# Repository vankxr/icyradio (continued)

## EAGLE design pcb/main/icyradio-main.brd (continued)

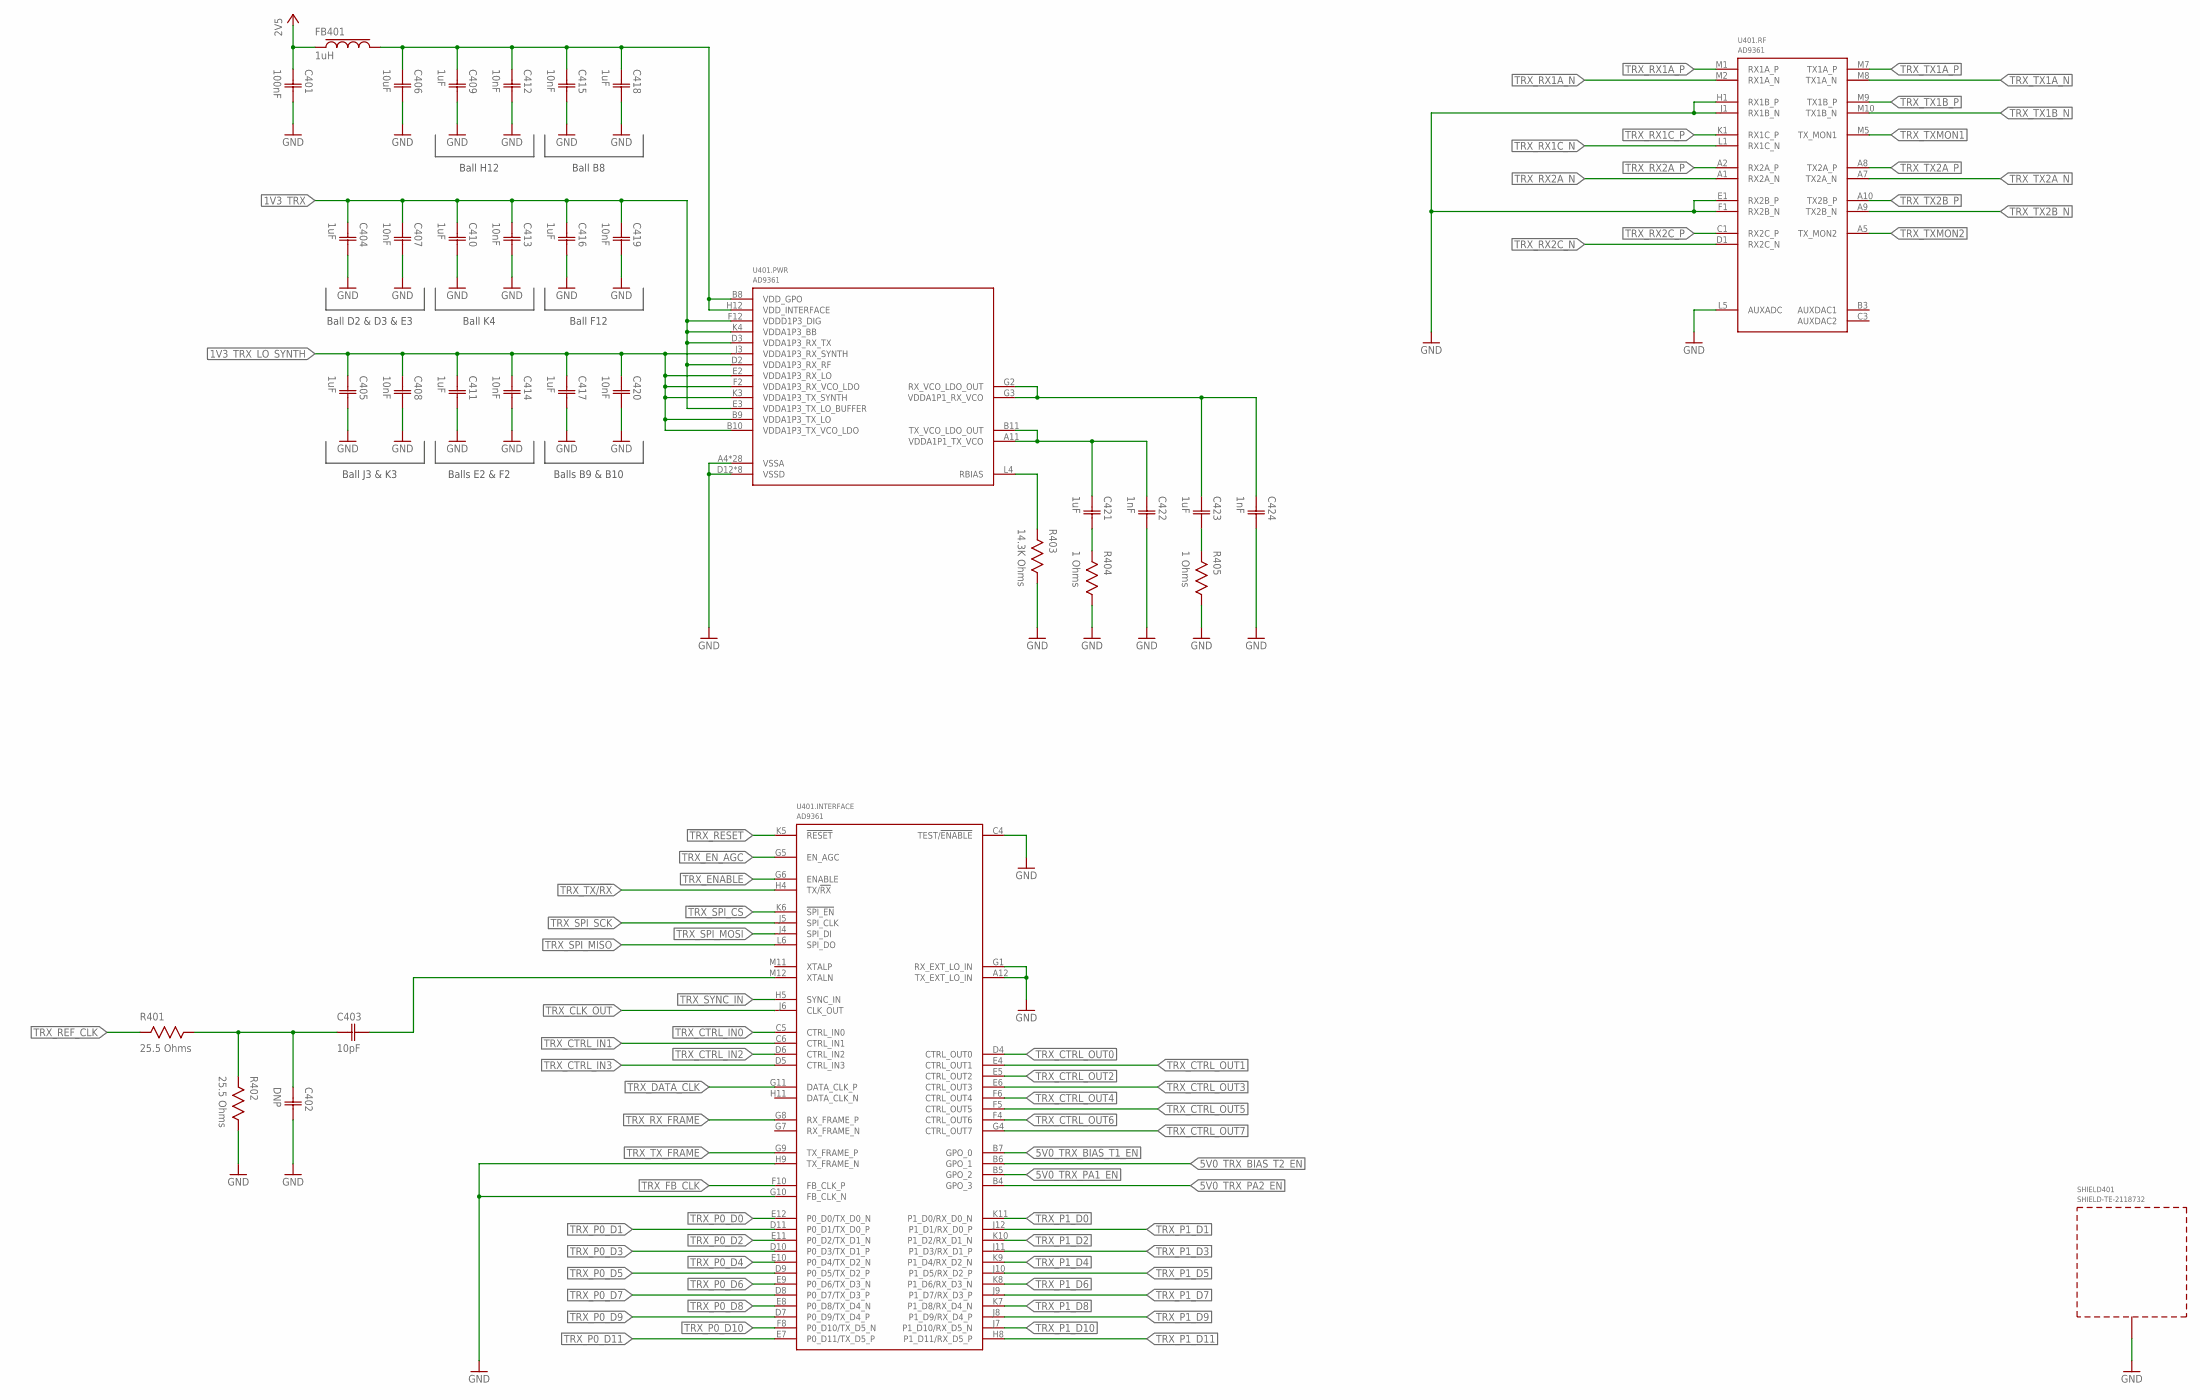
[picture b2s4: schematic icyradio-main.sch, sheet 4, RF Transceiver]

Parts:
C401: 100nF; CAP0402
C402: DNP; CAP0402
C403: 10pF; CAP0402
C404, C405, C409, C410, C411, C416, C417, C418, C421, C423: 1uF; CAP0402
C406: 10uF; CAP0402
C407, C408, C412, C413, C414, C415, C419, C420: 10nF; CAP0402
C422, C424: 1nF; CAP0402
FB401: 1uH; IND0603
R401, R402: 25.5 Ohms; RES0402
R403: 14.3K Ohms; RES0402
R404, R405: 1 Ohms; RES0402
SHIELD401: SHIELD-TE-2118732; 2118732
U401: AD9361; BGA144

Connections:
1V1_TRX_RX_VCO: C423.1 (C1), C424.1 (C1), U401.G2 (RX_VCO_LDO_OUT), U401.G3 (VDDA1P1_RX_VCO)
1V1_TRX_TX_VCO: C421.1 (C1), C422.1 (C1), U401.A11 (VDDA1P1_TX_VCO), U401.B11 (TX_VCO_LDO_OUT)
1V3_TRX: C404.1 (C1), C407.1 (C1), C410.1 (C1), C413.1 (C1), C416.1 (C1), C419.1 (C1), U401.D2 (VDDA1P3_RX_RF), U401.D3 (VDDA1P3_RX_TX), U401.E3 (VDDA1P3_TX_LO_BUFFER), U401.F12 (VDDD1P3_DIG), U401.K4 (VDDA1P3_BB); also elsewhere on the board
1V3_TRX_LO_SYNTH: C405.1 (C1), C408.1 (C1), C411.1 (C1), C414.1 (C1), C417.1 (C1), C420.1 (C1), U401.B9 (VDDA1P3_TX_LO), U401.B10 (VDDA1P3_TX_VCO_LDO), U401.E2 (VDDA1P3_RX_LO), U401.F2 (VDDA1P3_RX_VCO_LDO), U401.J3 (VDDA1P3_RX_SYNTH), U401.K3 (VDDA1P3_TX_SYNTH); also elsewhere on the board
2V5: C401.1 (C1), FB401.1; also elsewhere on the board
2V5_TRX_INTF_GPO_AUXDAC: C406.1 (C1), C409.1 (C1), C412.1 (C1), C415.1 (C1), C418.1 (C1), FB401.2, U401.B8 (VDD_GPO), U401.H12 (VDD_INTERFACE)
5V0_TRX_BIAS_T1_EN: U401.B7 (GPO_0); also elsewhere on the board
5V0_TRX_BIAS_T2_EN: U401.B6 (GPO_1); also elsewhere on the board
5V0_TRX_PA1_EN: U401.B5 (GPO_2); also elsewhere on the board
5V0_TRX_PA2_EN: U401.B4 (GPO_3); also elsewhere on the board
!TRX_RESET: U401.K5 (!RESET); also elsewhere on the board
!TRX_SPI_CS: U401.K6 (!SPI_EN); also elsewhere on the board
GND: C401.2 (C2), C402.2 (C2), C404.2 (C2), C405.2 (C2), C406.2 (C2), C407.2 (C2), C408.2 (C2), C409.2 (C2), C410.2 (C2), C411.2 (C2), C412.2 (C2), C413.2 (C2), C414.2 (C2), C415.2 (C2), C416.2 (C2), C417.2 (C2), C418.2 (C2), C419.2 (C2), C420.2 (C2), C422.2 (C2), C424.2 (C2), R402.1, R403.1, R404.1, R405.1, SHIELD401.1, SHIELD401.2, SHIELD401.3, SHIELD401.4, SHIELD401.5, SHIELD401.6, SHIELD401.7, SHIELD401.8, SHIELD401.9, SHIELD401.10, SHIELD401.11, SHIELD401.12, SHIELD401.13, SHIELD401.14, SHIELD401.15, SHIELD401.16, SHIELD401.17, SHIELD401.18, SHIELD401.19, SHIELD401.20, SHIELD401.21, SHIELD401.22, SHIELD401.23, SHIELD401.24, SHIELD401.25, SHIELD401.26, SHIELD401.27, SHIELD401.28, SHIELD401.29, SHIELD401.30, SHIELD401.31, SHIELD401.32, U401.A4 (VSSA), U401.A6 (VSSA), U401.A12 (TX_EXT_LO_IN), U401.B1 (VSSA), U401.B2 (VSSA), U401.B12 (VSSA), U401.C2 (VSSA), U401.C4 (TEST/!ENABLE), U401.C7 (VSSA), U401.C8 (VSSA), U401.C9 (VSSA), U401.C10 (VSSA), U401.C11 (VSSA), U401.C12 (VSSA), U401.D12 (VSSD), U401.E1 (RX2B_P), U401.F1 (RX2B_N), U401.F3 (VSSA), U401.F7 (VSSD), U401.F9 (VSSD), U401.F11 (VSSD), U401.G1 (RX_EXT_LO_IN), U401.G10 (FB_CLK_N), U401.G12 (VSSD), U401.H1 (RX1B_P), U401.H2 (VSSA), U401.H3 (VSSA), U401.H6 (VSSA), U401.H7 (VSSD), U401.H9 (TX_FRAME_N), U401.H10 (VSSD), U401.J1 (RX1B_N), U401.J2 (VSSA), U401.K2 (VSSA), U401.K12 (VSSD), U401.L2 (VSSA), U401.L3 (VSSA), U401.L5 (AUXADC), U401.L7 (VSSA), U401.L8 (VSSA), U401.L9 (VSSA), U401.L10 (VSSA), U401.L11 (VSSA), U401.L12 (VSSA), U401.M4 (VSSA), U401.M6 (VSSA); also elsewhere on the board
unnamed: R403.2, U401.L4 (RBIAS)
unnamed: C421.2 (C2), R404.2
unnamed: C423.2 (C2), R405.2
TRX_CLK_OUT: U401.J6 (CLK_OUT); also elsewhere on the board
TRX_CTRL_IN0: U401.C5 (CTRL_IN0); also elsewhere on the board
TRX_CTRL_IN1: U401.C6 (CTRL_IN1); also elsewhere on the board
TRX_CTRL_IN2: U401.D6 (CTRL_IN2); also elsewhere on the board
TRX_CTRL_IN3: U401.D5 (CTRL_IN3); also elsewhere on the board
TRX_CTRL_OUT0: U401.D4 (CTRL_OUT0); also elsewhere on the board
TRX_CTRL_OUT1: U401.E4 (CTRL_OUT1); also elsewhere on the board
TRX_CTRL_OUT2: U401.E5 (CTRL_OUT2); also elsewhere on the board
TRX_CTRL_OUT3: U401.E6 (CTRL_OUT3); also elsewhere on the board
TRX_CTRL_OUT4: U401.F6 (CTRL_OUT4); also elsewhere on the board
TRX_CTRL_OUT5: U401.F5 (CTRL_OUT5); also elsewhere on the board
TRX_CTRL_OUT6: U401.F4 (CTRL_OUT6); also elsewhere on the board
TRX_CTRL_OUT7: U401.G4 (CTRL_OUT7); also elsewhere on the board
TRX_DATA_CLK: U401.G11 (DATA_CLK_P); also elsewhere on the board
TRX_ENABLE: U401.G6 (ENABLE); also elsewhere on the board
TRX_EN_AGC: U401.G5 (EN_AGC); also elsewhere on the board
TRX_FB_CLK: U401.F10 (FB_CLK_P); also elsewhere on the board
TRX_P0_D0: U401.E12 (P0_D0/TX_D0_N); also elsewhere on the board
TRX_P0_D1: U401.D11 (P0_D1/TX_D0_P); also elsewhere on the board
TRX_P0_D2: U401.E11 (P0_D2/TX_D1_N); also elsewhere on the board
TRX_P0_D3: U401.D10 (P0_D3/TX_D1_P); also elsewhere on the board
TRX_P0_D4: U401.E10 (P0_D4/TX_D2_N); also elsewhere on the board
TRX_P0_D5: U401.D9 (P0_D5/TX_D2_P); also elsewhere on the board
TRX_P0_D6: U401.E9 (P0_D6/TX_D3_N); also elsewhere on the board
TRX_P0_D7: U401.D8 (P0_D7/TX_D3_P); also elsewhere on the board
TRX_P0_D8: U401.E8 (P0_D8/TX_D4_N); also elsewhere on the board
TRX_P0_D9: U401.D7 (P0_D9/TX_D4_P); also elsewhere on the board
TRX_P0_D10: U401.F8 (P0_D10/TX_D5_N); also elsewhere on the board
TRX_P0_D11: U401.E7 (P0_D11/TX_D5_P); also elsewhere on the board
TRX_P1_D0: U401.K11 (P1_D0/RX_D0_N); also elsewhere on the board
TRX_P1_D1: U401.J12 (P1_D1/RX_D0_P); also elsewhere on the board
TRX_P1_D2: U401.K10 (P1_D2/RX_D1_N); also elsewhere on the board
TRX_P1_D3: U401.J11 (P1_D3/RX_D1_P); also elsewhere on the board
TRX_P1_D4: U401.K9 (P1_D4/RX_D2_N); also elsewhere on the board
TRX_P1_D5: U401.J10 (P1_D5/RX_D2_P); also elsewhere on the board
TRX_P1_D6: U401.K8 (P1_D6/RX_D3_N); also elsewhere on the board
TRX_P1_D7: U401.J9 (P1_D7/RX_D3_P); also elsewhere on the board
TRX_P1_D8: U401.K7 (P1_D8/RX_D4_N); also elsewhere on the board
TRX_P1_D9: U401.J8 (P1_D9/RX_D4_P); also elsewhere on the board
TRX_P1_D10: U401.J7 (P1_D10/RX_D5_N); also elsewhere on the board
TRX_P1_D11: U401.H8 (P1_D11/RX_D5_P); also elsewhere on the board
TRX_REF_CLK: R401.2; also elsewhere on the board
TRX_REF_CLK_DIV: C402.1 (C1), C403.1 (C1), R401.1, R402.2
TRX_RX1A_N: U401.M2 (RX1A_N); also elsewhere on the board
TRX_RX1A_P: U401.M1 (RX1A_P); also elsewhere on the board
TRX_RX1C_N: U401.L1 (RX1C_N); also elsewhere on the board
TRX_RX1C_P: U401.K1 (RX1C_P); also elsewhere on the board
TRX_RX2A_N: U401.A1 (RX2A_N); also elsewhere on the board
TRX_RX2A_P: U401.A2 (RX2A_P); also elsewhere on the board
TRX_RX2C_N: U401.D1 (RX2C_N); also elsewhere on the board
TRX_RX2C_P: U401.C1 (RX2C_P); also elsewhere on the board
TRX_RX_FRAME: U401.G8 (RX_FRAME_P); also elsewhere on the board
TRX_SPI_MISO: U401.L6 (SPI_DO); also elsewhere on the board
TRX_SPI_MOSI: U401.J4 (SPI_DI); also elsewhere on the board
TRX_SPI_SCK: U401.J5 (SPI_CLK); also elsewhere on the board
TRX_SYNC_IN: U401.H5 (SYNC_IN); also elsewhere on the board
TRX_TX1A_N: U401.M8 (TX1A_N); also elsewhere on the board
TRX_TX1A_P: U401.M7 (TX1A_P); also elsewhere on the board
TRX_TX1B_N: U401.M10 (TX1B_N); also elsewhere on the board
TRX_TX1B_P: U401.M9 (TX1B_P); also elsewhere on the board
TRX_TX2A_N: U401.A7 (TX2A_N); also elsewhere on the board
TRX_TX2A_P: U401.A8 (TX2A_P); also elsewhere on the board
TRX_TX2B_N: U401.A9 (TX2B_N); also elsewhere on the board
TRX_TX2B_P: U401.A10 (TX2B_P); also elsewhere on the board
TRX_TX/!RX: U401.H4 (TX/!RX); also elsewhere on the board
TRX_TXMON1: U401.M5 (TX_MON1); also elsewhere on the board
TRX_TXMON2: U401.A5 (TX_MON2); also elsewhere on the board
TRX_TX_FRAME: U401.G9 (TX_FRAME_P); also elsewhere on the board
TRX_XTALN: C403.2 (C2), U401.M12 (XTALN)

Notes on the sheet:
Ball J3 & K3
Balls E2 & F2
Balls B9 & B10
Ball D2 & D3 & E3
Ball K4
Ball F12
Ball H12
Ball B8

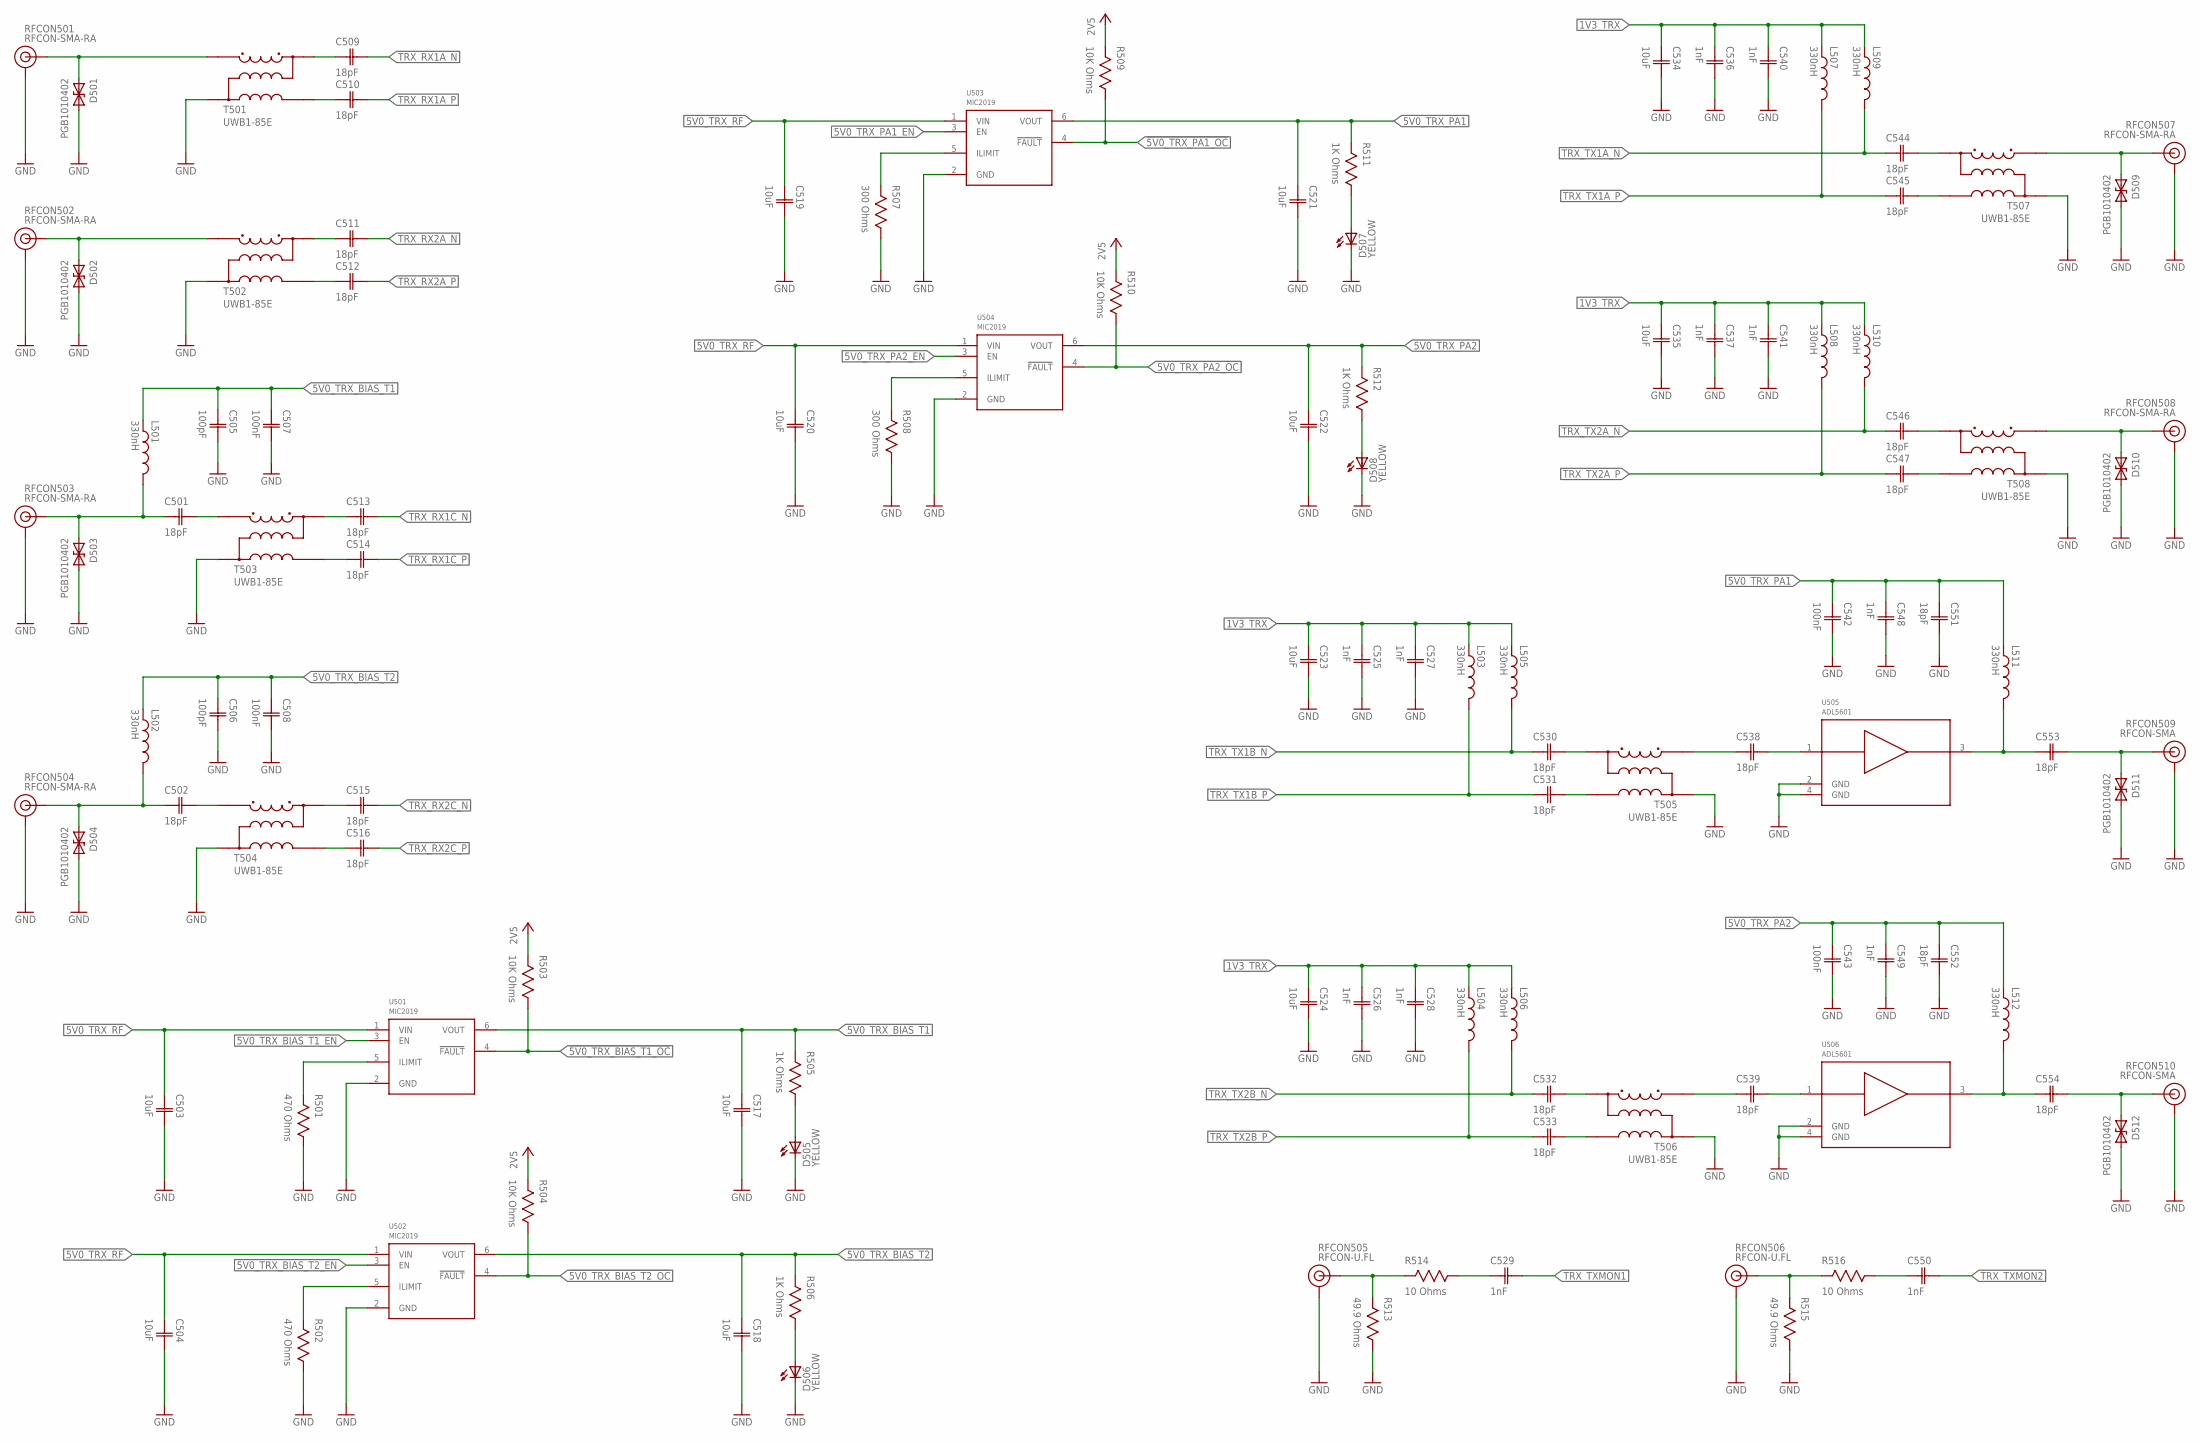
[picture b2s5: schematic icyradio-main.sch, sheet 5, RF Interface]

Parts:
C501, C502, C509, C510, C511, C512, C513, C514, C515, C516, C530, C531, C532, C533, C538, C539, C544, C545, C546, C547, C551, C552, C553, C554: 18pF; CAP0402
C503, C504, C517, C518, C519, C520, C521, C522: 10uF; CAP0603
C505, C506: 100pF; CAP0402
C507, C508, C542, C543: 100nF; CAP0402
C523, C524, C534, C535: 10uF; CAP0402
C525, C526, C527, C528, C529, C536, C537, C540, C541, C548, C549, C550: 1nF; CAP0402
D501, D502, D503, D504, D509, D510, D511, D512: PGB1010402; TVS0402
D505, D506, D507, D508: LED0603; 0603
L501, L502: 330nH; IND0805
L503, L504, L505, L506, L507, L508, L509, L510, L511, L512: 330nH; IND0603
R501, R502: 470 Ohms; RES0402
R503, R504, R509, R510: 10K Ohms; RES0402
R505, R506, R511, R512: 1K Ohms; RES0402
R507, R508: 300 Ohms; RES0402
R513, R515: 49.9 Ohms; RES0402
R514, R516: 10 Ohms; RES0402
RFCON501, RFCON502, RFCON503, RFCON504, RFCON507, RFCON508: RFCON-SMA-RA; SMA-RA
RFCON505, RFCON506: RFCON-U.FL; U.FL
RFCON509, RFCON510: RFCON-SMA; SMA
T501, T502, T503, T504, T505, T506, T507, T508: UWB1-85E; UWB1
U501, U502, U503, U504: MIC2019; SOT23-6
U505, U506: ADL5601; SOT89

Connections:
1V3_TRX: C523.1 (C1), C524.1 (C1), C525.1 (C1), C526.1 (C1), C527.1 (C1), C528.1 (C1), C534.1 (C1), C535.1 (C1), C536.1 (C1), C537.1 (C1), C540.1 (C1), C541.1 (C1), L503.1, L504.1, L505.1, L506.1, L507.1, L508.1, L509.1, L510.1; also elsewhere on the board
2V5: R503.2, R504.2, R509.2, R510.2; also elsewhere on the board
5V0_TRX_BIAS_T1: C505.1 (C1), C507.1 (C1), C517.1 (C1), L501.1, R505.2, U501.6 (VOUT)
5V0_TRX_BIAS_T1_EN: U501.3 (EN); also elsewhere on the board
5V0_TRX_BIAS_T2: C506.1 (C1), C508.1 (C1), C518.1 (C1), L502.1, R506.2, U502.6 (VOUT)
5V0_TRX_BIAS_T2_EN: U502.3 (EN); also elsewhere on the board
5V0_TRX_PA1: C521.1 (C1), C542.1 (C1), C548.1 (C1), C551.1 (C1), L511.1, R511.2, U503.6 (VOUT)
5V0_TRX_PA1_EN: U503.3 (EN); also elsewhere on the board
5V0_TRX_PA2: C522.1 (C1), C543.1 (C1), C549.1 (C1), C552.1 (C1), L512.1, R512.2, U504.6 (VOUT)
5V0_TRX_PA2_EN: U504.3 (EN); also elsewhere on the board
5V0_TRX_RF: C503.1 (C1), C504.1 (C1), C519.1 (C1), C520.1 (C1), U501.1 (VIN), U502.1 (VIN), U503.1 (VIN), U504.1 (VIN); also elsewhere on the board
!5V0_TRX_BIAS_T1_OC: R503.1, U501.4 (!FAULT); also elsewhere on the board
!5V0_TRX_BIAS_T2_OC: R504.1, U502.4 (!FAULT); also elsewhere on the board
!5V0_TRX_PA1_OC: R509.1, U503.4 (!FAULT); also elsewhere on the board
!5V0_TRX_PA2_OC: R510.1, U504.4 (!FAULT); also elsewhere on the board
GND: C503.2 (C2), C504.2 (C2), C505.2 (C2), C506.2 (C2), C507.2 (C2), C508.2 (C2), C517.2 (C2), C518.2 (C2), C519.2 (C2), C520.2 (C2), C521.2 (C2), C522.2 (C2), C523.2 (C2), C524.2 (C2), C525.2 (C2), C526.2 (C2), C527.2 (C2), C528.2 (C2), C534.2 (C2), C535.2 (C2), C536.2 (C2), C537.2 (C2), C540.2 (C2), C541.2 (C2), C542.2 (C2), C543.2 (C2), C548.2 (C2), C549.2 (C2), C551.2 (C2), C552.2 (C2), D501.2, D502.2, D503.2, D504.2, D505.C, D506.C, D507.C, D508.C, D509.2, D510.2, D511.2, D512.2, R501.1, R502.1, R507.1, R508.1, R513.1, R515.1, RFCON501.GND@0 (GND), RFCON501.GND@1 (GND), RFCON501.GND@2 (GND), RFCON501.GND@3 (GND), RFCON502.GND@0 (GND), RFCON502.GND@1 (GND), RFCON502.GND@2 (GND), RFCON502.GND@3 (GND), RFCON503.GND@0 (GND), RFCON503.GND@1 (GND), RFCON503.GND@2 (GND), RFCON503.GND@3 (GND), RFCON504.GND@0 (GND), RFCON504.GND@1 (GND), RFCON504.GND@2 (GND), RFCON504.GND@3 (GND), RFCON505.P$1 (GND), RFCON505.P$2 (GND), RFCON506.P$1 (GND), RFCON506.P$2 (GND), RFCON507.GND@0 (GND), RFCON507.GND@1 (GND), RFCON507.GND@2 (GND), RFCON507.GND@3 (GND), RFCON508.GND@0 (GND), RFCON508.GND@1 (GND), RFCON508.GND@2 (GND), RFCON508.GND@3 (GND), RFCON509.GND@0 (GND), RFCON509.GND@1 (GND), RFCON509.GND@2 (GND), RFCON509.GND@3 (GND), RFCON510.GND@0 (GND), RFCON510.GND@1 (GND), RFCON510.GND@2 (GND), RFCON510.GND@3 (GND), T501.2 (PRI2), T502.2 (PRI2), T503.2 (PRI2), T504.2 (PRI2), T505.2 (PRI2), T506.2 (PRI2), T507.2 (PRI2), T508.2 (PRI2), U501.2 (GND), U502.2 (GND), U503.2 (GND), U504.2 (GND), U505.2 (GND), U505.4 (GND), U506.2 (GND), U506.4 (GND); also elsewhere on the board
unnamed: C533.2 (C2), T506.4 (SEC2)
unnamed: C532.2 (C2), T506.5 (SEC1)
unnamed: D508.A, R512.1
unnamed: C529.1 (C1), R514.1
unnamed: D507.A, R511.1
unnamed: C550.1 (C1), R516.1
unnamed: C545.2 (C2), T507.4 (SEC2)
unnamed: C544.2 (C2), T507.5 (SEC1)
unnamed: C547.2 (C2), T508.4 (SEC2)
unnamed: C546.2 (C2), T508.5 (SEC1)
unnamed: C510.1 (C1), T501.4 (SEC2)
unnamed: C509.1 (C1), T501.5 (SEC1)
unnamed: C512.1 (C1), T502.4 (SEC2)
unnamed: C511.1 (C1), T502.5 (SEC1)
unnamed: D505.A, R505.1
unnamed: D506.A, R506.1
unnamed: C516.1 (C1), T504.4 (SEC2)
unnamed: C515.1 (C1), T504.5 (SEC1)
unnamed: R507.2, U503.5 (ILIMIT)
unnamed: C514.1 (C1), T503.4 (SEC2)
unnamed: C513.1 (C1), T503.5 (SEC1)
unnamed: C531.2 (C2), T505.4 (SEC2)
unnamed: C530.2 (C2), T505.5 (SEC1)
unnamed: R508.2, U504.5 (ILIMIT)
unnamed: R501.2, U501.5 (ILIMIT)
unnamed: R502.2, U502.5 (ILIMIT)
TRX_RX1A: D501.1, RFCON501.SIGNAL, T501.3 (PRI1)
TRX_RX1A_N: C509.2 (C2); also elsewhere on the board
TRX_RX1A_P: C510.2 (C2); also elsewhere on the board
TRX_RX1C_ACC: C501.2 (C2), T503.3 (PRI1)
TRX_RX1C_DCC: C501.1 (C1), D503.1, L501.2, RFCON503.SIGNAL
TRX_RX1C_N: C513.2 (C2); also elsewhere on the board
TRX_RX1C_P: C514.2 (C2); also elsewhere on the board
TRX_RX2A: D502.1, RFCON502.SIGNAL, T502.3 (PRI1)
TRX_RX2A_N: C511.2 (C2); also elsewhere on the board
TRX_RX2A_P: C512.2 (C2); also elsewhere on the board
TRX_RX2C_ACC: C502.2 (C2), T504.3 (PRI1)
TRX_RX2C_DCC: C502.1 (C1), D504.1, L502.2, RFCON504.SIGNAL
TRX_RX2C_N: C515.2 (C2); also elsewhere on the board
TRX_RX2C_P: C516.2 (C2); also elsewhere on the board
TRX_TX1A: D509.1, RFCON507.SIGNAL, T507.3 (PRI1)
TRX_TX1A_N: C544.1 (C1), L509.2; also elsewhere on the board
TRX_TX1A_P: C545.1 (C1), L507.2; also elsewhere on the board
TRX_TX1B: C538.1 (C1), T505.3 (PRI1)
TRX_TX1B_AMP_ACC: C553.2 (C2), D511.1, RFCON509.SIGNAL
TRX_TX1B_AMP_DCC: C553.1 (C1), L511.2, U505.3 (RFOUT)
TRX_TX1B_DCC: C538.2 (C2), U505.1 (RFIN)
TRX_TX1B_N: C530.1 (C1), L505.2; also elsewhere on the board
TRX_TX1B_P: C531.1 (C1), L503.2; also elsewhere on the board
TRX_TX2A: D510.1, RFCON508.SIGNAL, T508.3 (PRI1)
TRX_TX2A_N: C546.1 (C1), L510.2; also elsewhere on the board
TRX_TX2A_P: C547.1 (C1), L508.2; also elsewhere on the board
TRX_TX2B: C539.1 (C1), T506.3 (PRI1)
TRX_TX2B_AMP: C554.2 (C2), D512.1, RFCON510.SIGNAL
TRX_TX2B_AMP_DCC: C554.1 (C1), L512.2, U506.3 (RFOUT)
TRX_TX2B_DCC: C539.2 (C2), U506.1 (RFIN)
TRX_TX2B_N: C532.1 (C1), L506.2; also elsewhere on the board
TRX_TX2B_P: C533.1 (C1), L504.2; also elsewhere on the board
TRX_TXMON1: C529.2 (C2); also elsewhere on the board
TRX_TXMON1_Z50: R513.2, R514.2, RFCON505.P$3 (SIGNAL)
TRX_TXMON2: C550.2 (C2); also elsewhere on the board
TRX_TXMON2_Z50: R515.2, R516.2, RFCON506.P$3 (SIGNAL)

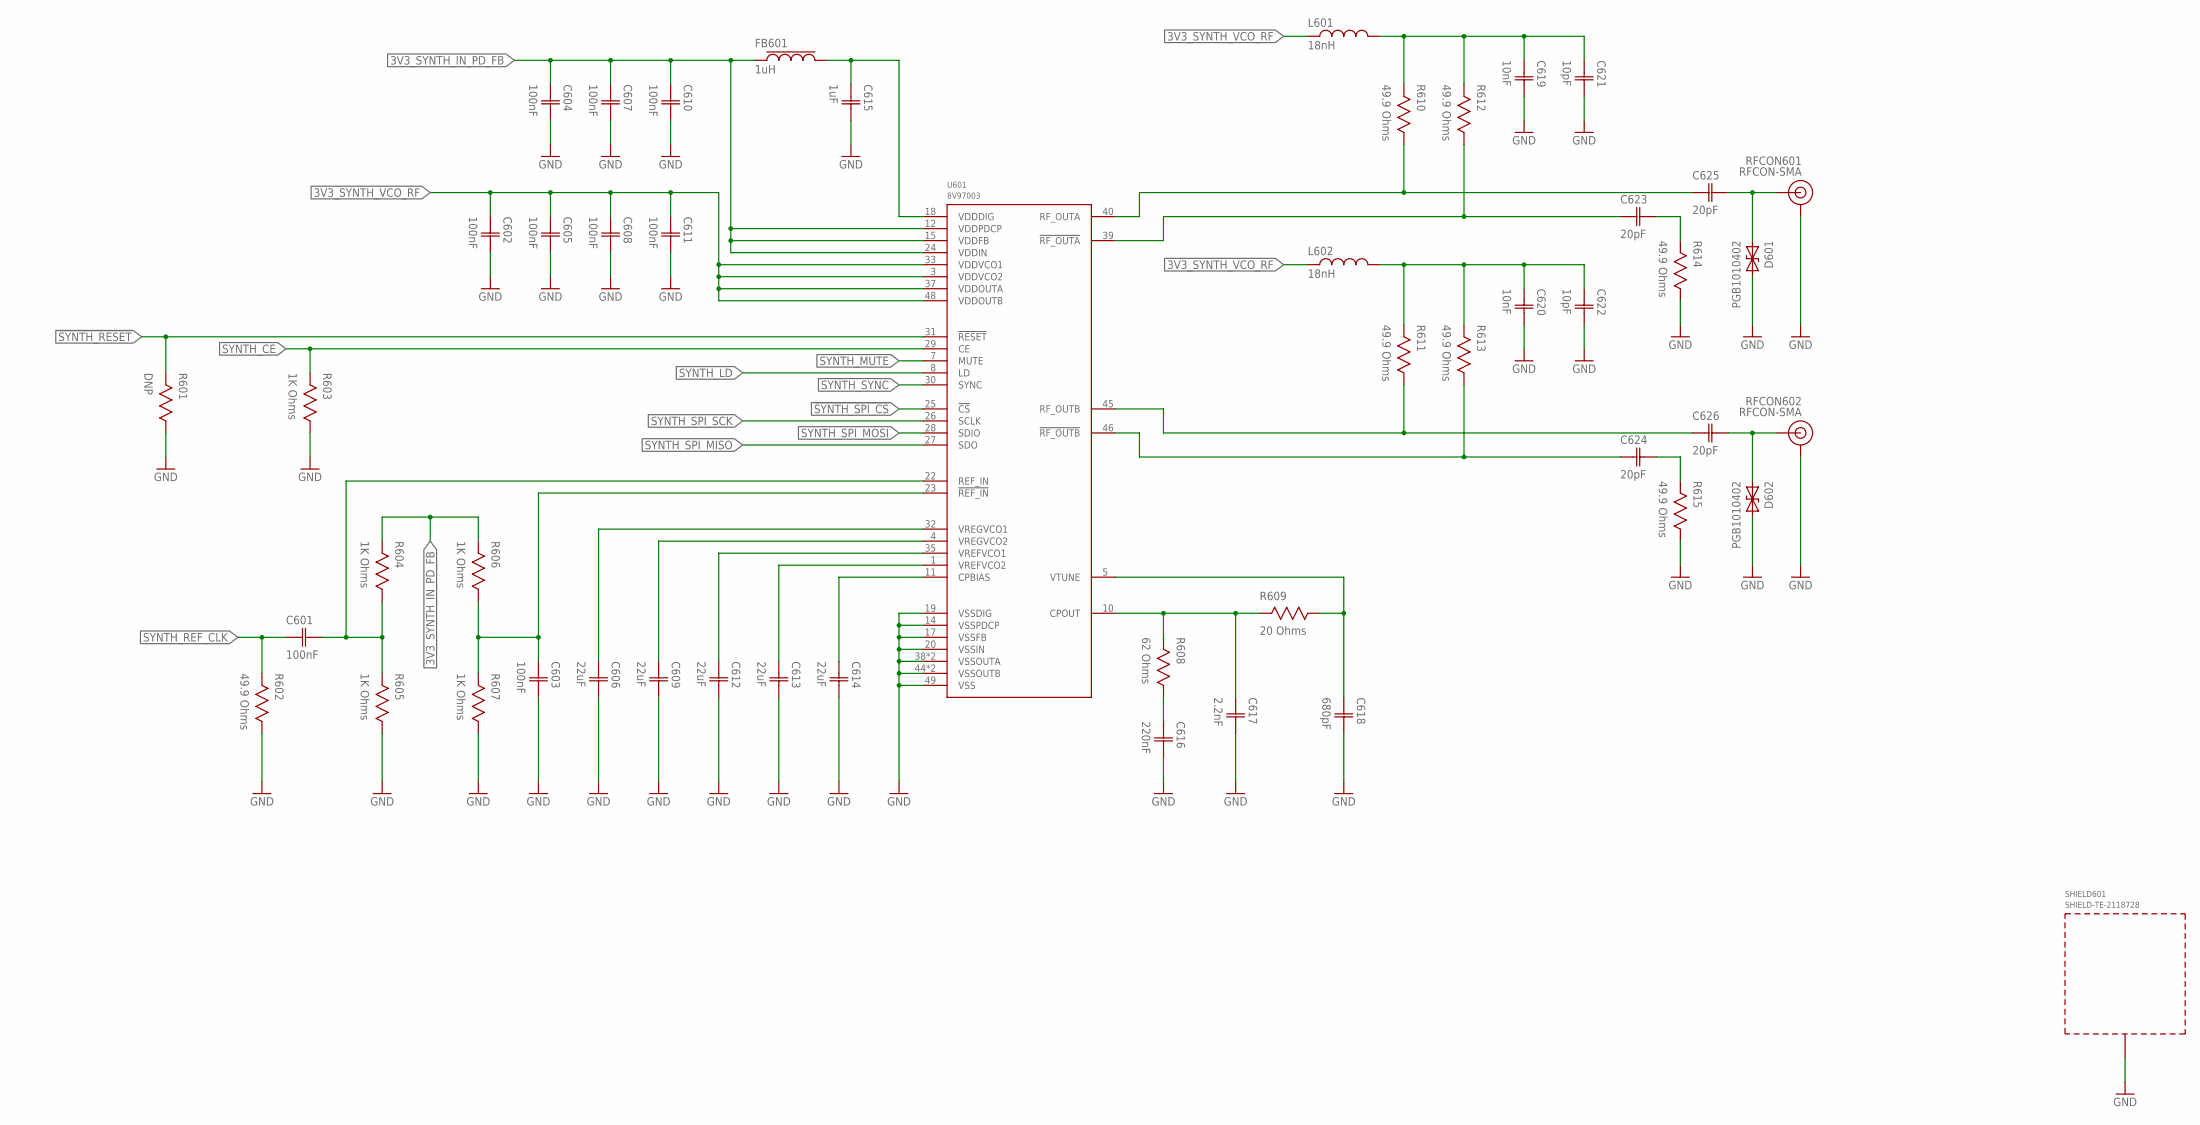
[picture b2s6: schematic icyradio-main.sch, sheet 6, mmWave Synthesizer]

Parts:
C601, C602, C603, C604, C605, C607, C608, C610, C611: 100nF; CAP0402
C606, C609, C612, C613, C614: 22uF; CAP0402
C615: 1uF; CAP0402
C616: 220nF; CAP0402
C617: 2.2nF; CAP0402
C618: 680pF; CAP0402
C619, C620: 10nF; CAP0402
C621, C622: 10pF; CAP0402
C623, C624, C625, C626: 20pF; CAP0402
D601, D602: PGB1010402; TVS0402
FB601: 1uH; IND0603
L601, L602: 18nH; IND0402
R601: DNP; RES0402
R602, R610, R611, R612, R613, R614, R615: 49.9 Ohms; RES0402
R603, R604, R605, R606, R607: 1K Ohms; RES0402
R608: 62 Ohms; RES0402
R609: 20 Ohms; RES0402
RFCON601, RFCON602: RFCON-SMA; SMA
SHIELD601: SHIELD-TE-2118728; 2118728
U601: 8V97003; VFQFPN48

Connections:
3V3_SYNTH_IN_PD_FB: C604.1 (C1), C607.1 (C1), C610.1 (C1), FB601.1, R604.2, R606.2, U601.12 (VDDPDCP), U601.15 (VDDFB), U601.24 (VDDIN); also elsewhere on the board
3V3_SYNTH_VCO_RF: C602.1 (C1), C605.1 (C1), C608.1 (C1), C611.1 (C1), L601.1, L602.1, U601.3 (VDDVCO2), U601.33 (VDDVCO1), U601.37 (VDDOUTA), U601.48 (VDDOUTB); also elsewhere on the board
!SYNTH_RESET: R601.2, U601.31 (!RESET); also elsewhere on the board
!SYNTH_SPI_CS: U601.25 (!CS); also elsewhere on the board
GND: C602.2 (C2), C603.2 (C2), C604.2 (C2), C605.2 (C2), C606.2 (C2), C607.2 (C2), C608.2 (C2), C609.2 (C2), C610.2 (C2), C611.2 (C2), C612.2 (C2), C613.2 (C2), C614.2 (C2), C615.2 (C2), C616.2 (C2), C617.2 (C2), C618.2 (C2), C619.2 (C2), C620.2 (C2), C621.2 (C2), C622.2 (C2), D601.2, D602.2, R601.1, R602.1, R603.1, R605.1, R607.1, R614.1, R615.1, RFCON601.GND@0 (GND), RFCON601.GND@1 (GND), RFCON601.GND@2 (GND), RFCON601.GND@3 (GND), RFCON602.GND@0 (GND), RFCON602.GND@1 (GND), RFCON602.GND@2 (GND), RFCON602.GND@3 (GND), SHIELD601.1, SHIELD601.2, SHIELD601.3, SHIELD601.4, SHIELD601.5, SHIELD601.6, SHIELD601.7, SHIELD601.8, SHIELD601.9, SHIELD601.10, SHIELD601.11, SHIELD601.12, SHIELD601.13, SHIELD601.14, SHIELD601.15, SHIELD601.16, U601.14 (VSSPDCP), U601.17 (VSSFB), U601.19 (VSSDIG), U601.20 (VSSIN), U601.38 (VSSOUTA), U601.41 (VSSOUTA), U601.44 (VSSOUTB), U601.47 (VSSOUTB), U601.49 (VSS); also elsewhere on the board
unnamed: C615.1 (C1), FB601.2, U601.18 (VDDDIG)
unnamed: C616.1 (C1), R608.1
SYNTH_CE: R603.2, U601.29 (CE); also elsewhere on the board
SYNTH_CPBIAS: C614.1 (C1), U601.11 (CPBIAS)
SYNTH_CPOUT: C617.1 (C1), R608.2, R609.2, U601.10 (CPOUT)
SYNTH_LD: U601.8 (LD); also elsewhere on the board
SYNTH_MUTE: U601.7 (MUTE); also elsewhere on the board
SYNTH_REFIN_N: C603.1 (C1), R606.1, R607.2, U601.23 (!REF_IN)
SYNTH_REFIN_P: C601.2 (C2), R604.1, R605.2, U601.22 (REF_IN)
SYNTH_REF_CLK: C601.1 (C1), R602.2; also elsewhere on the board
SYNTH_RFOUTA_ACC_N: C623.2 (C2), R614.2
SYNTH_RFOUTA_ACC_P: C625.2 (C2), D601.1, RFCON601.SIGNAL
SYNTH_RFOUTA_BIAS: C619.1 (C1), C621.1 (C1), L601.2, R610.2, R612.2
SYNTH_RFOUTA_N: C623.1 (C1), R612.1, U601.39 (!RF_OUTA)
SYNTH_RFOUTA_P: C625.1 (C1), R610.1, U601.40 (RF_OUTA)
SYNTH_RFOUTB_ACC_N: C624.2 (C2), R615.2
SYNTH_RFOUTB_ACC_P: C626.2 (C2), D602.1, RFCON602.SIGNAL
SYNTH_RFOUTB_BIAS: C620.1 (C1), C622.1 (C1), L602.2, R611.2, R613.2
SYNTH_RFOUTB_N: C624.1 (C1), R613.1, U601.46 (!RF_OUTB)
SYNTH_RFOUTB_P: C626.1 (C1), R611.1, U601.45 (RF_OUTB)
SYNTH_SPI_MISO: U601.27 (SDO); also elsewhere on the board
SYNTH_SPI_MOSI: U601.28 (SDIO); also elsewhere on the board
SYNTH_SPI_SCK: U601.26 (SCLK); also elsewhere on the board
SYNTH_SYNC: U601.30 (SYNC); also elsewhere on the board
SYNTH_VREFVCO1: C612.1 (C1), U601.35 (VREFVCO1)
SYNTH_VREFVCO2: C613.1 (C1), U601.1 (VREFVCO2)
SYNTH_VREGVCO1: C606.1 (C1), U601.32 (VREGVCO1)
SYNTH_VREGVCO2: C609.1 (C1), U601.4 (VREGVCO2)
SYNTH_VTUNE: C618.1 (C1), R609.1, U601.5 (VTUNE)
